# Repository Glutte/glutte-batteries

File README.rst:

Mesure de l'état de charge de la batterie
=========================================

Les nouvelles (juillet 2019) batteries au plomb nécessitent une nouvelle
approche pour mesurer leur état de charge.

Mesurer la tension ne suffit pas, d'abord parce que la différence de tension
entre batterie pleine et vide est faible, d'autre part parce que la tension
mesurée dépend fortement du courant de dé-/charge.

Proposition
-----------

Mesurer le courant à intervalle régulier (p.ex. à 10Hz) et intégrer le courant
pour calculer une charge accumulée ou extraite de la batterie (A * s = Coulomb).

Besoins
-------

Quand le niveau de charge des batteries est trop bas, il faut couper des
consommateurs. Il est possible de commuter les groupes de consommateurs suivants:

- Balise 70cm
- Mode relais QRP/QRO
- Alimentation Relais
- Alimentation Raspberry Pi, WiFi et autres consommateurs 5V restants

Afin que le relais puisse indiquer le niveau de charge, un port série est
utilisé entre le coulomb-mètre et la glutt-o-matique (unidirectionnel). Pour la
surveillance ainsi que pour d'autres applications, un deuxième port série transmet
les mêmes informations à un Raspberry Pi connecté à Internet.

Le colomb-mètre doit donc comporter trois commutations à relais, qui peuvent à
leur tour commuter des relais de puissance.

Quelques définitions
--------------------

Tension nominale: Tension d'un élément chargé au repos à 25°C : 2.1V/élément soit
12.6V pour la traditionnelle batterie dite de 12V. C'est ce que vous devez lire
(à la précision de la mesure près) sur une batterie que vous avez chargée et
ensuite débranchée pendant une nuit.

Tension de floating (tension de charge d'entretien):
Tension à laquelle on peut maintenir en permanence un accumulateur
pour être sûr qu'il soit chargé au moment où en a besoin : 2.25 à 2.28/élément à
25°C. Cette valeur devrait être corrigée de 0.005V en plus ou en moins par degré
centigrade selon que la température descend ou monte.
A -10°C c'est 2.36V et à +40°C 2.21V.

Tension de recharge:
Tension maximum à laquelle on peut charger la batterie (mais pas la laisser en
permanence). 2.3 à 2.4V/élément toujours à 25°C et avec le même coefficient de
température de 0.005V/°C. Soit 13.8 à 14.4V pour un bloc 12V à 25°C.
Attention à prendre aussi en considération les pics de courte durée si la
tension est bruitée.

Evitez de décharger la batterie en dessous de 11.9V, car vous commencez à
décharger profondément la batterie.

Risque de gel: Une batterie profondément déchargée risque le gel!

+---------+---------------+------------------------+--------------------+
|  Baumé  | Densité H2SO4 | Etat de charge         | Température de gel |
+=========+===============+========================+====================+
| 13 à 23 | 1.099 à 1.190 | Profondément déchargée | entre -7C et -27C  |
+---------+---------------+------------------------+--------------------+
| 24 à 29 | 1.200 à 1.252 | Moyenne                | entre -27C et -52C |
+---------+---------------+------------------------+--------------------+
| 30 à 32 | 1.262 à 1.285 | Pleine                 | plus bas que -52C  |
+---------+---------------+------------------------+--------------------+

Composants
----------

Boitier: Hammond RZ0214C

Shunt: muRata 3020-01096-0

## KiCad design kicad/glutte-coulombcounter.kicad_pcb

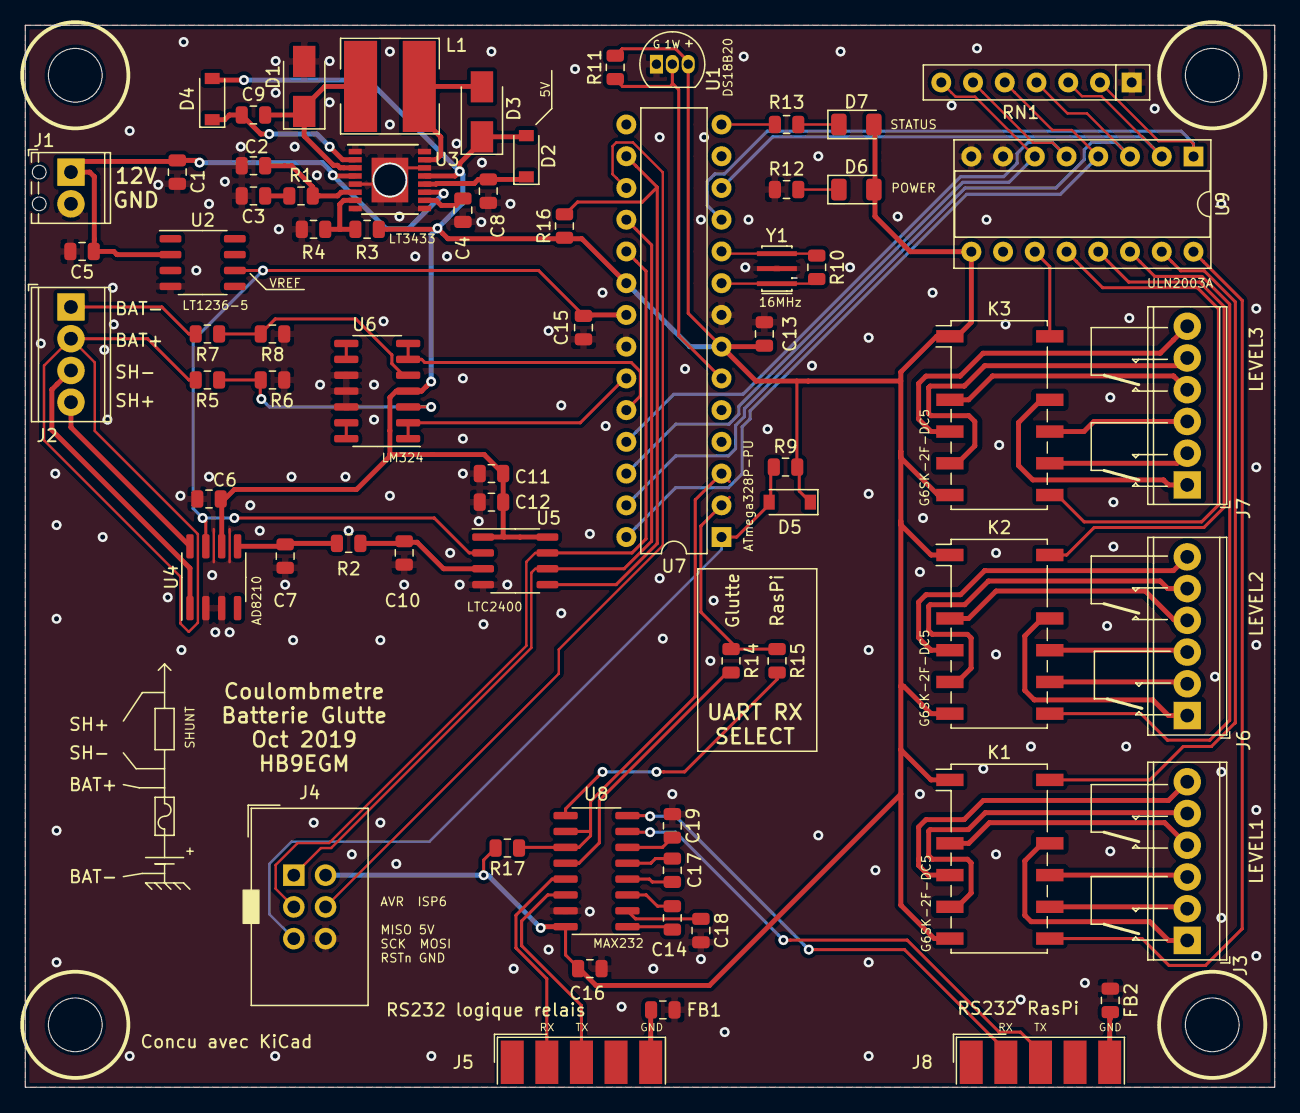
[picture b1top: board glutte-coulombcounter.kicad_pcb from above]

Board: 2 copper layers, 100.0 x 85.0 mm, 72 parts (0 on the bottom side), 81 nets.

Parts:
C1: 2.2u; C_0805_2012Metric
C2: 330p; C_0805_2012Metric
C3: 1000p; C_0805_2012Metric
C4: 0.01u; C_0805_2012Metric
C5, C6, C8, C9, C13, C15: 0.1u; C_0805_2012Metric
C7, C10: DNF; C_0805_2012Metric
C11: 4.7u; C_0805_2012Metric
C12: 0.1uF; C_0805_2012Metric
C14, C16, C17, C18, C19: 1u; C_0805_2012Metric
D1: B160-E3; D_SMA
D2, D4, D5: 1N4148; D_SOD-123
D3: B120-E3; D_SMA
D6: LED_PWR; LED_1206_3216Metric
D7: LED_STATUS; LED_1206_3216Metric
FB1, FB2: DNF; L_0805_2012Metric
H1, H2, H3, H4: M4; MountingHole_4.3mm_M4
J1: 12V; TerminalBlock_Phoenix_MPT-0,5-2-2.54_1x02_P2.54mm_Horizontal
J2: Measure; TerminalBlock_Phoenix_MPT-0,5-4-2.54_1x04_P2.54mm_Horizontal
J3: K1; TerminalBlock_Phoenix_MPT-0,5-6-2.54_1x06_P2.54mm_Horizontal
J4: AVR-ISP-6; IDC-Header_2x03_P2.54mm_Vertical
J5: Glutte; DSUB-9_Male_EdgeMount_P2.77mm
J6: K2; TerminalBlock_Phoenix_MPT-0,5-6-2.54_1x06_P2.54mm_Horizontal
J7: K3; TerminalBlock_Phoenix_MPT-0,5-6-2.54_1x06_P2.54mm_Horizontal
J8: Raspi; DSUB-9_Male_EdgeMount_P2.77mm
K1, K2, K3: G6SK-2F-DC5; Relay_DPDT_Omron_G6SK-2F
L1: 100uH; Sumida_CDRH6D28
R1: 68k; R_0805_2012Metric
R2: 51; R_0805_2012Metric
R3: 300k; R_0805_2012Metric
R4: 97.6k; R_0805_2012Metric
R5, R7: 300k/1%; R_0805_2012Metric
R6, R8: 100k/1%; R_0805_2012Metric
R9: 10k; R_0805_2012Metric
R10: 1M; R_0805_2012Metric
R11, R16, R17: 4k7; R_0805_2012Metric
R12, R13: 330; R_0805_2012Metric
R14: 0R; R_0805_2012Metric
R15: DNF; R_0805_2012Metric
RN1: 2k2; R_Array_SIP7
U1: DS18B20; TO-92_Inline
U2: LT1236-5; SO-8_3.9x4.9mm_P1.27mm
U3: LT3433; TSSOP-16-1EP_4.4x5mm_P0.65mm
U4: AD8210; SOIC-8_3.9x4.9mm_P1.27mm
U5: LTC2400; SO-8_3.9x4.9mm_P1.27mm
U6: LM324; SOIC-14_3.9x8.7mm_P1.27mm
U7: ATmega328P-PU; DIP-28_W7.62mm
U8: MAX232; SOIC-16_3.9x9.9mm_P1.27mm
U9: ULN2003A; DIP-16_W7.62mm_Socket
Y1: CSTNE16M0V530000R0; Resonator_SMD_muRata_CSTxExxV-3Pin_3.0x1.1mm_HandSoldering

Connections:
+5VA: C6.1, C11.1, C12.1, C13.1, C16.1, D2.2, D3.1, D4.2, D5.1, D6.2, D7.2, J4.2, K1.1, K1.6, K2.1, K2.6, K3.1, K3.6, R3.2, R9.2, R11.2, R16.1, R17.2, U1.3, U3.13, U4.6, U5.1, U5.8, U6.4, U7.7, U7.20, U8.16, U9.9
+12V: C1.1, C5.1, J1.1, U2.2, U3.4, U3.11
+BATT: J2.2, R5.2
-BATT: J2.1, R7.2
/1WIRE: R11.1, U1.2, U7.6
/ADC0: U6.1, U6.2, U7.23
/ADC1: U6.6, U6.7, U7.24
/MISO: J4.1, U5.6, U7.18
/MOSI: J4.4, U7.17
/RESETn: D5.2, J4.5, R9.1, U7.1
/RXD: R14.1, R15.1, U7.2
/Relays/K1_RESET: RN1.2, U7.11, U9.1
/Relays/K1_SET: RN1.3, U7.12, U9.2
/Relays/K2_RESET: RN1.4, U7.27, U9.3
/Relays/K2_SET: RN1.5, U7.28, U9.4
/Relays/K3_RESET: RN1.6, U7.25, U9.5
/Relays/K3_SET: RN1.7, U7.26, U9.6
/SCK: J4.3, U5.7, U7.19
/SHUNT+: J2.4, U4.8
/SHUNT-: J2.3, U4.1
/SSn: R16.2, U5.5, U7.16
/STATUS: R13.2, U7.14
/TXD: R17.1, U7.3, U8.10, U8.11
GNDA: C1.2, C2.2, C3.2, C4.2, C5.2, C6.2, C7.2, C8.1, C10.2, C11.2, C12.2, C13.2, C15.2, C16.2, C18.2, C19.1, D1.2, FB1.1, FB2.1, J1.2, J4.6, R4.1, R6.1, R8.1, R12.1, RN1.1, U1.1, U2.4, U3.1, U3.5, U3.8, U3.9, U3.14, U3.16, U3.17, U4.2, U4.3, U5.4, U6.10, U6.11, U6.12, U7.8, U7.22, U8.15, U9.7, U9.8, Y1.2
unnamed: C2.1, R1.2, U3.6
unnamed: C3.1, R1.1
unnamed: C4.1, U3.10
unnamed: C7.1, R2.2, U4.5
unnamed: C8.2, D2.1, U3.12
unnamed: C9.1, D4.1, U3.2
unnamed: C9.2, D1.1, L1.1, U3.3
unnamed: C10.1, R2.1, U5.3
unnamed: C14.1, U8.1
unnamed: C14.2, U8.3
unnamed: C17.1, U8.4
unnamed: C17.2, U8.5
unnamed: C18.1, U8.2
unnamed: C19.2, U8.6
unnamed: D3.2, L1.2, U3.15
unnamed: D6.1, R12.2
unnamed: D7.1, R13.1
unnamed: FB1.2, J5.5
unnamed: FB2.2, J8.5
unnamed: J3.1, K1.10
unnamed: J3.2, K1.8
unnamed: J3.3, K1.9
unnamed: J3.4, K1.3
unnamed: J3.5, K1.5
unnamed: J3.6, K1.4
unnamed: J5.2, U8.13
unnamed: J5.3, U8.14
unnamed: J6.1, K2.10
unnamed: J6.2, K2.8
unnamed: J6.3, K2.9
unnamed: J6.4, K2.3
unnamed: J6.5, K2.5
unnamed: J6.6, K2.4
unnamed: J7.1, K3.10
unnamed: J7.2, K3.8
unnamed: J7.3, K3.9
unnamed: J7.4, K3.3
unnamed: J7.5, K3.5
unnamed: J7.6, K3.4
unnamed: J8.2, U8.8
unnamed: J8.3, U8.7
unnamed: K1.7, U9.16
unnamed: K1.12, U9.15
unnamed: K2.7, U9.14
unnamed: K2.12, U9.13
unnamed: K3.7, U9.12
unnamed: K3.12, U9.11
unnamed: R3.1, R4.2, U3.7
unnamed: R5.1, R6.2, U6.3
unnamed: R7.1, R8.2, U6.5
unnamed: R10.1, U7.10, Y1.3
unnamed: R10.2, U7.9, Y1.1
unnamed: R14.2, U8.12
unnamed: R15.2, U8.9
unnamed: U6.8, U6.9
unnamed: U6.13, U6.14
VREF: C15.1, U2.6, U4.7, U5.2, U7.21

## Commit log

2019-07-24 Add first schematic
2019-07-24 Set footprints, add LEDs
2019-07-24 Place and route PCB
2019-07-24 Add doc
2019-07-24 Fix README table
2019-07-24 Change LM324 footprint to SOIC
2019-07-24 Rework some routing
2019-08-19 Update TODO, minor routing
2019-09-09 Move power supply to separate sheet
2019-09-09 Add relays
2019-10-18 Add second UART output for Raspi
2019-10-19 Update README with description of needs
2019-10-19 Add sw skeleton
2019-10-19 Add gitignore
2019-10-19 Add resistor network on relay control signals
2019-10-19 Add pullups on CSn and UART TX
2019-10-19 Add timer initialisation
2019-10-19 Add EEPROM load/store code
2019-10-19 Add watchdog
2019-10-19 Restructure lib, add uart
2019-10-19 Add acknowledgements
2019-10-21 Add minor remarks and comments in sw
2019-10-21 Change R and C to 0805, improve silkscreen
2019-10-21 Run DRC and ERC
2019-10-22 Minor routing changes
2019-10-22 sw: rename elf to sw.elf
2019-10-22 Correct wrong DCDC inductor
2019-10-22 Add Ampere to back silkscreen and update MPN
2019-10-24 Pull in some Arduino code so that libraries are easier to use
2019-10-25 Add new LTC2400 library
2019-10-26 Add preliminary mAh accumulator
2019-10-26 Print out current_capacity
2019-10-27 system_timer atomicity and integration interval calculation
2019-11-03 Move timer stuff to common
2019-11-03 Add relay toggle code
2019-11-03 Rework timer_t to use microseconds
2019-11-03 Add thresholds calculation
2019-11-03 Add some clarifications
2019-11-04 Specify MAX232 package
2019-11-17 Add ADC measurements
2019-11-17 Fix fuse settings to use crystal, not ext clock
2019-11-17 Use correct ISR for timer
2019-11-17 Add debug and wdt reset inside loop
2019-11-17 Change type of relay hold time variable
2019-11-17 Fix CAPACITY length print
2019-11-17 Fix interval calculation
2019-11-17 Replace C11 by 2.2uF instead of 4.7uF
2019-11-17 Add some LTC2400 debug
2019-11-17 Additional changes in SPI
2019-11-19 Fix LTC2400 readout
2019-12-28 Refresh schematic library
2019-12-28 Use explicit enum for battery voltage measurements
2019-12-28 Add config.h
2019-12-29 Set proper ADC reference selection
2019-12-29 Read ADCL before ADCH
2020-04-16 Check relay toggling functionality
2020-04-16 Disable DBG by default
2020-04-25 Fix loading of EEPROM and As to mAh conversion
2020-04-25 Status LED shows CPU sleeping
2020-04-26 Set max cap to 1650 Ah
2020-05-03 Refine thresholds
2020-05-03 Output Relay state
2020-10-30 Add disjoncteur state message
2020-10-30 Set startup cap to a conservative 1000Ah
2021-02-25 Properly setup CTC mode for timer
    The previous setup was out of spec, and overflowed at 255 instead of 195
2021-03-21 Set startup cap to 1650Ah
2023-05-01 Change startup capacity
